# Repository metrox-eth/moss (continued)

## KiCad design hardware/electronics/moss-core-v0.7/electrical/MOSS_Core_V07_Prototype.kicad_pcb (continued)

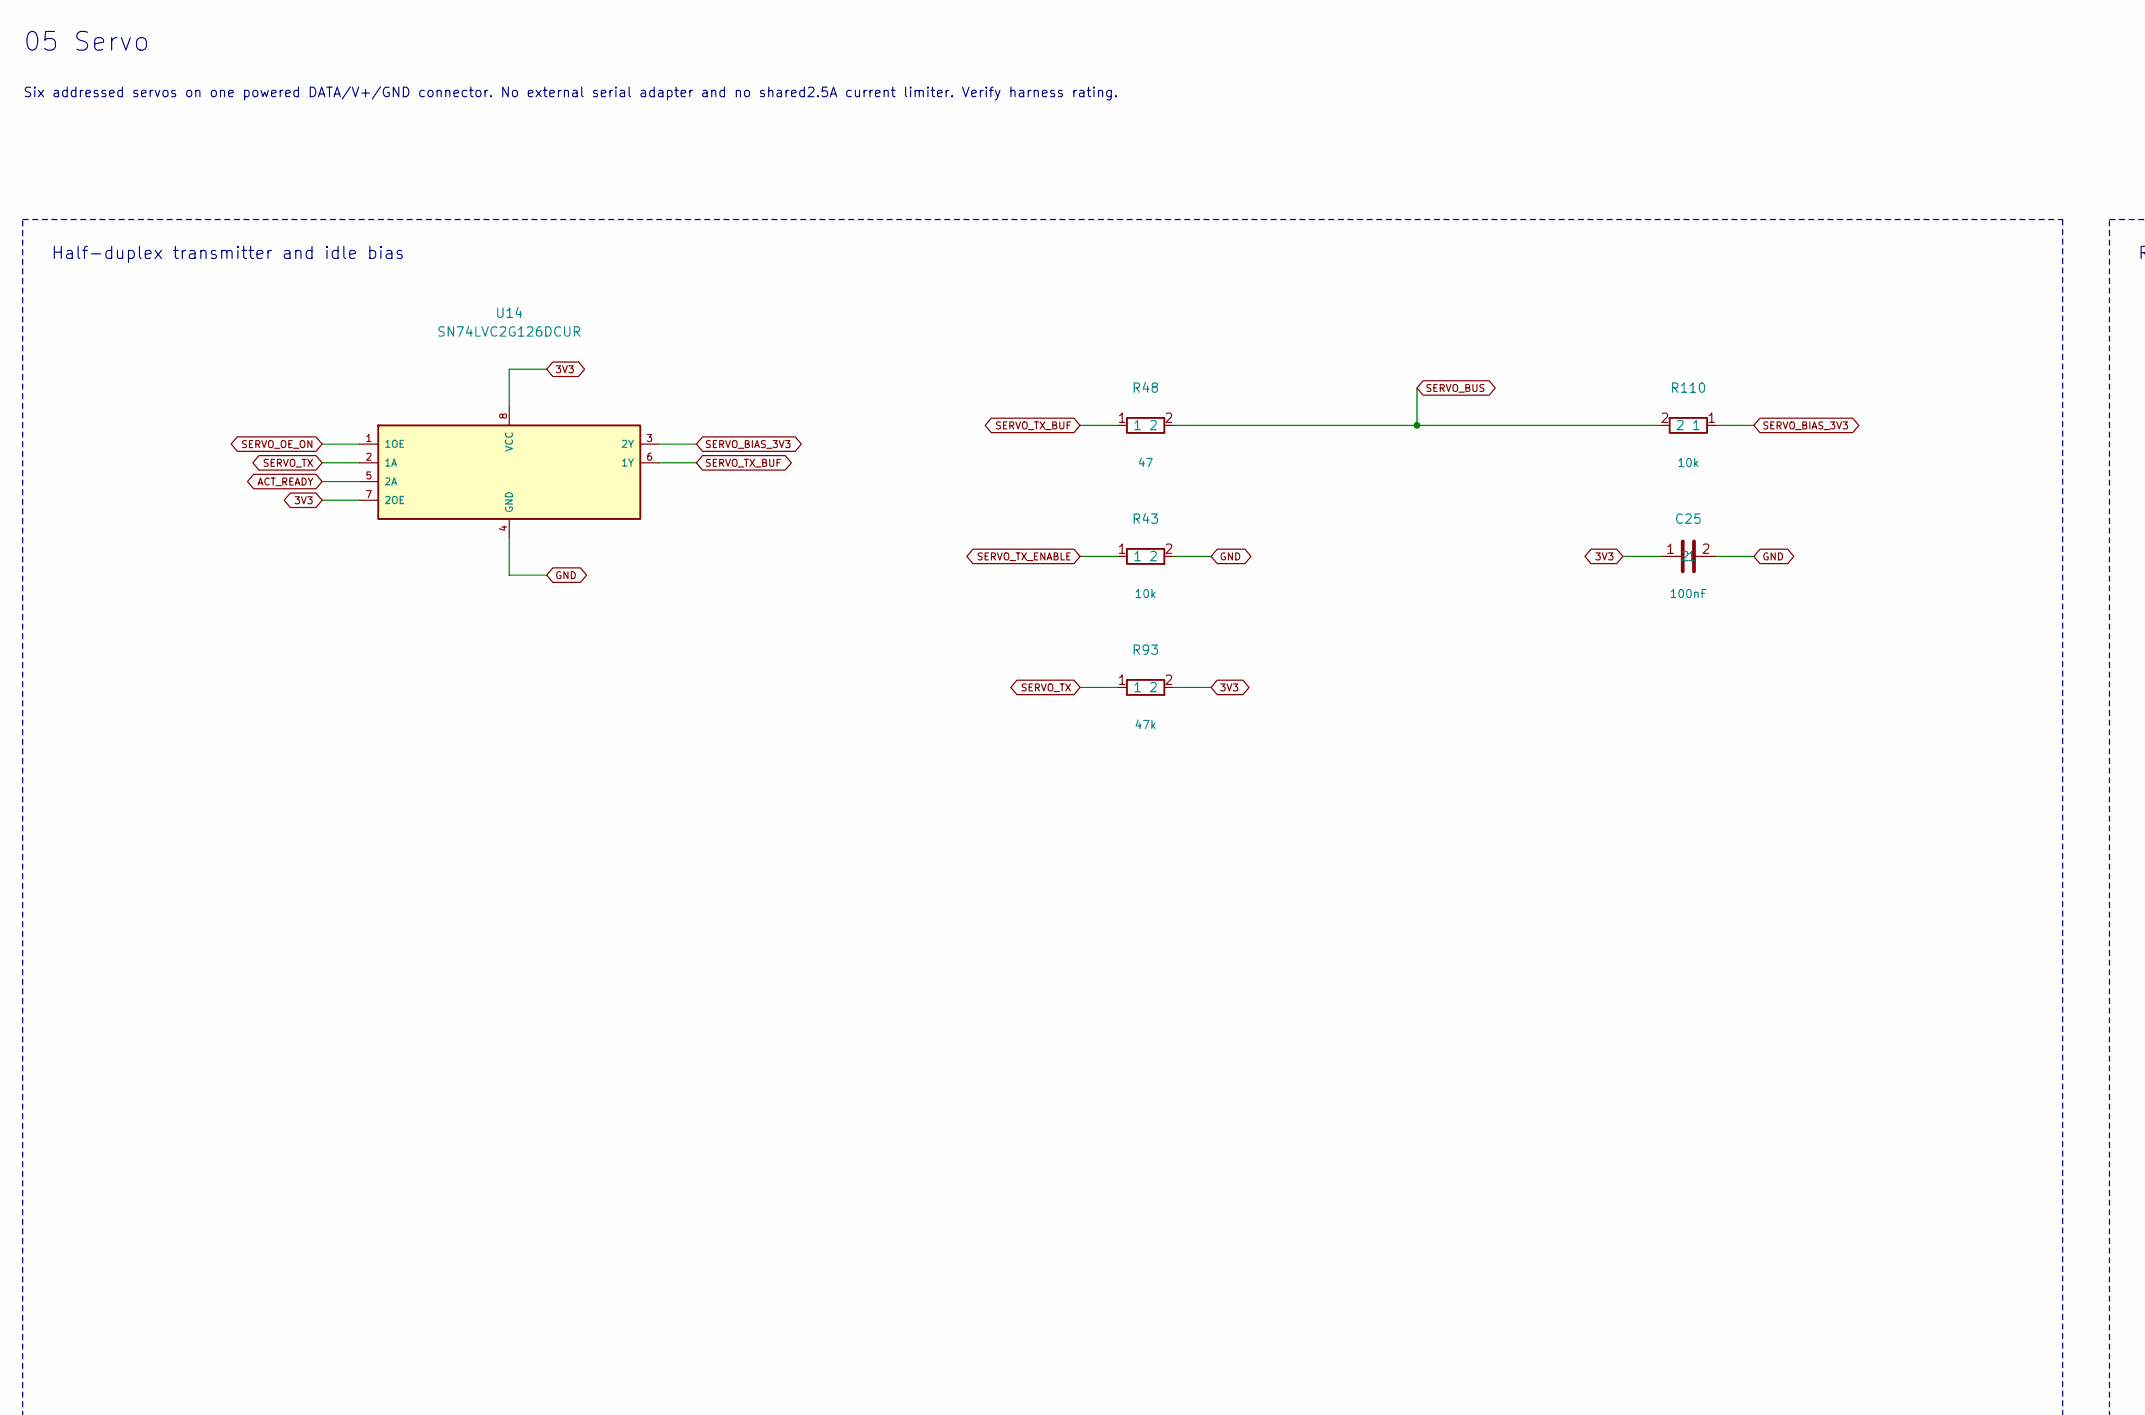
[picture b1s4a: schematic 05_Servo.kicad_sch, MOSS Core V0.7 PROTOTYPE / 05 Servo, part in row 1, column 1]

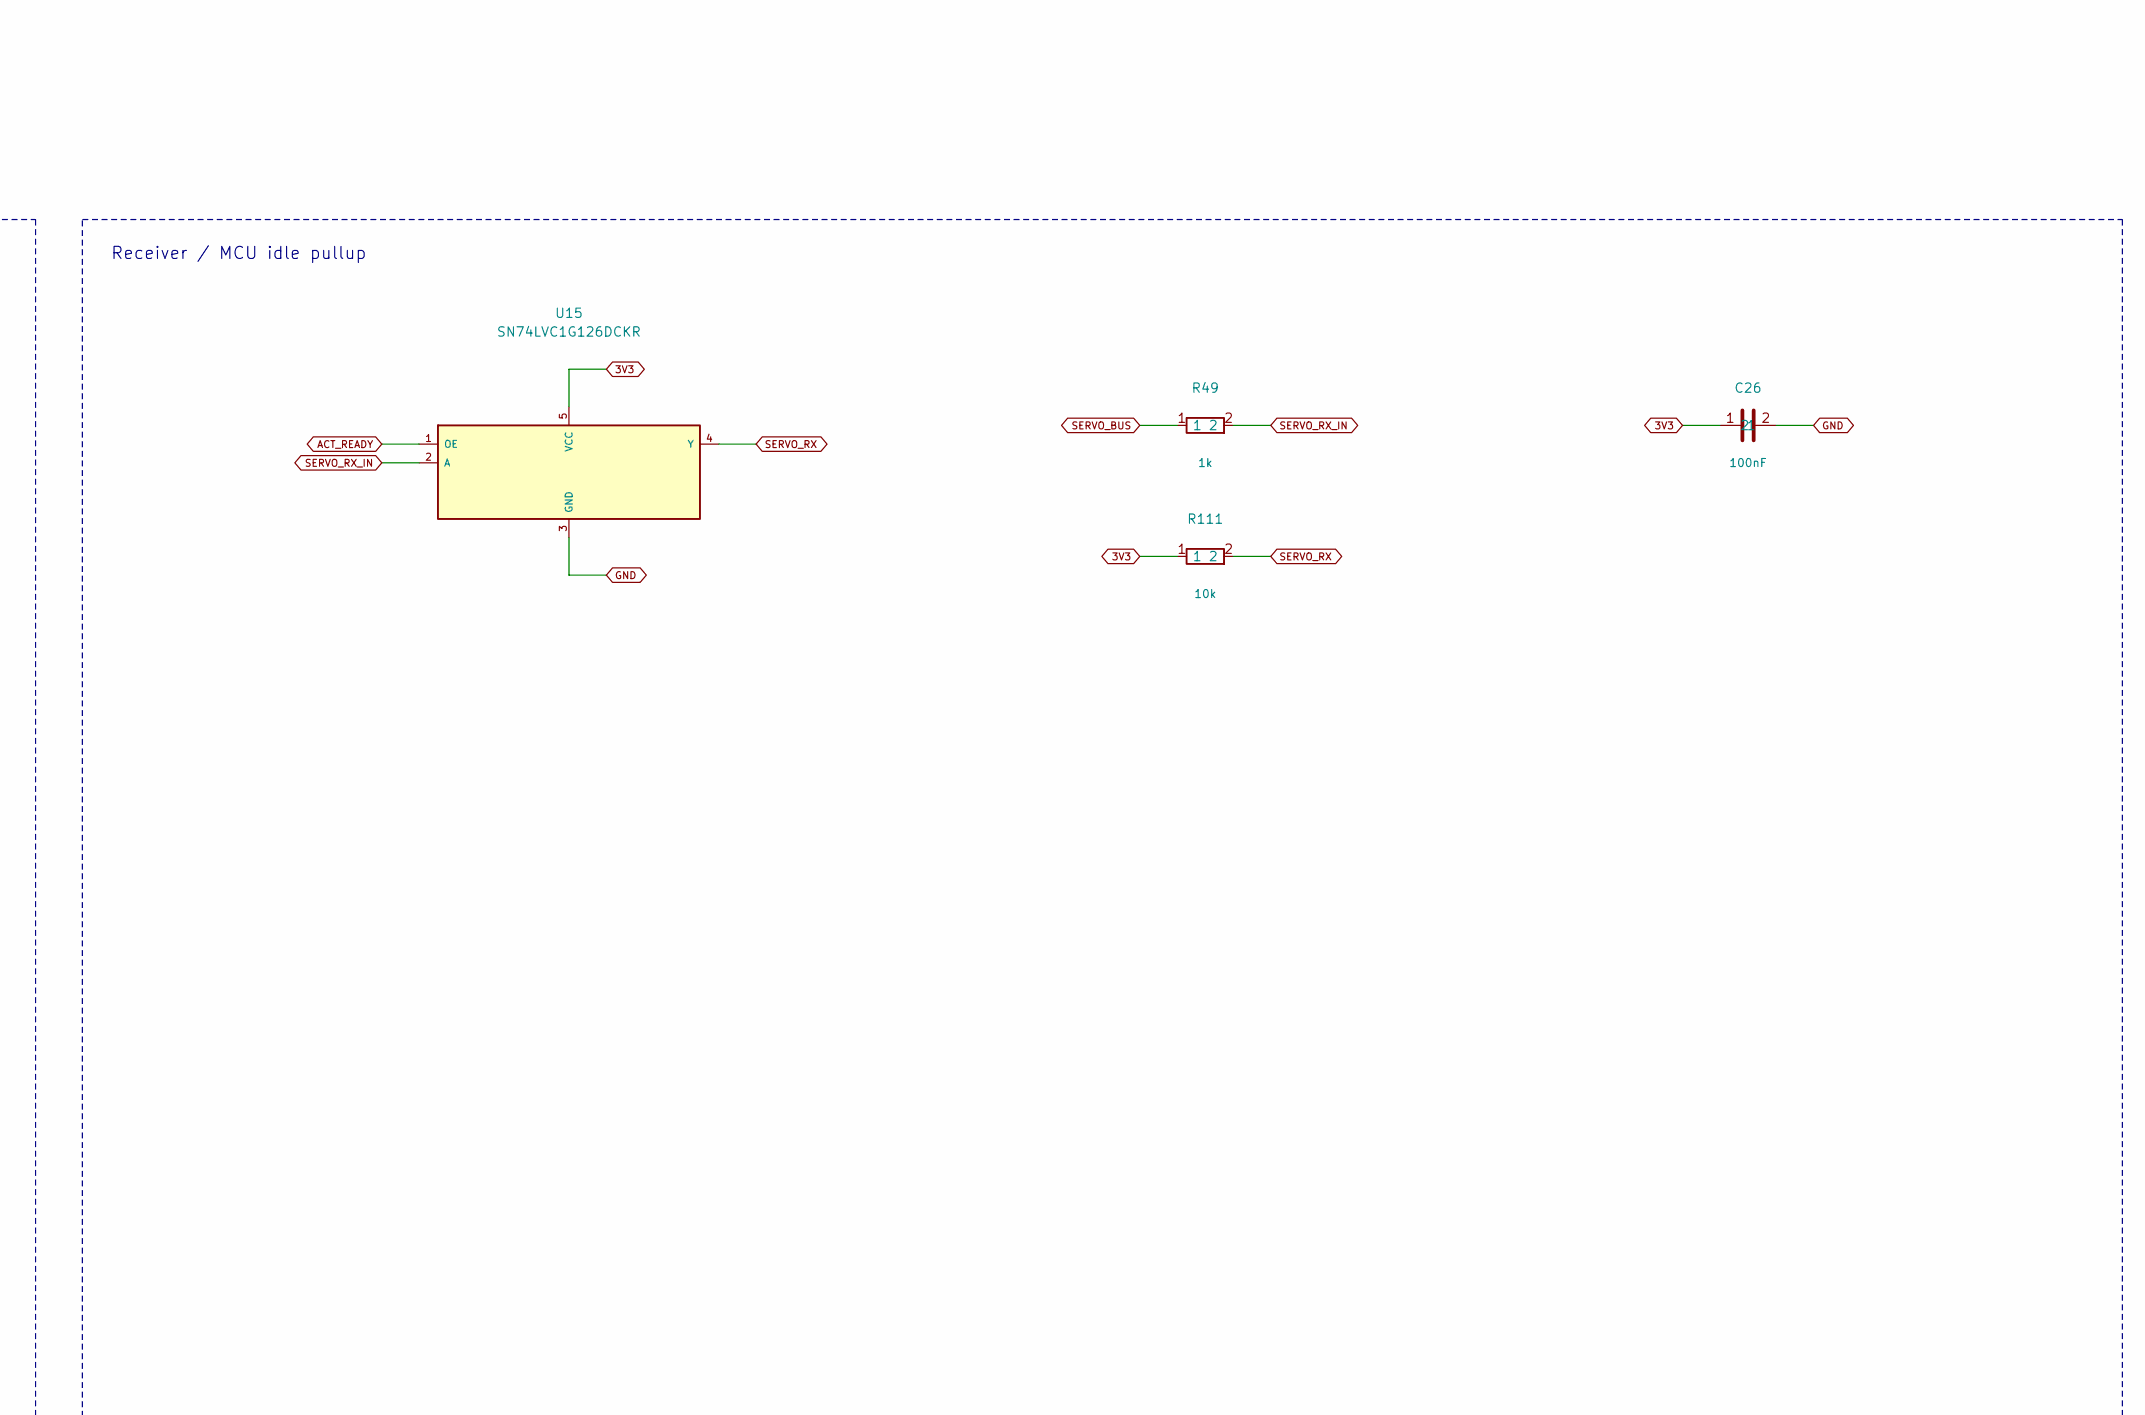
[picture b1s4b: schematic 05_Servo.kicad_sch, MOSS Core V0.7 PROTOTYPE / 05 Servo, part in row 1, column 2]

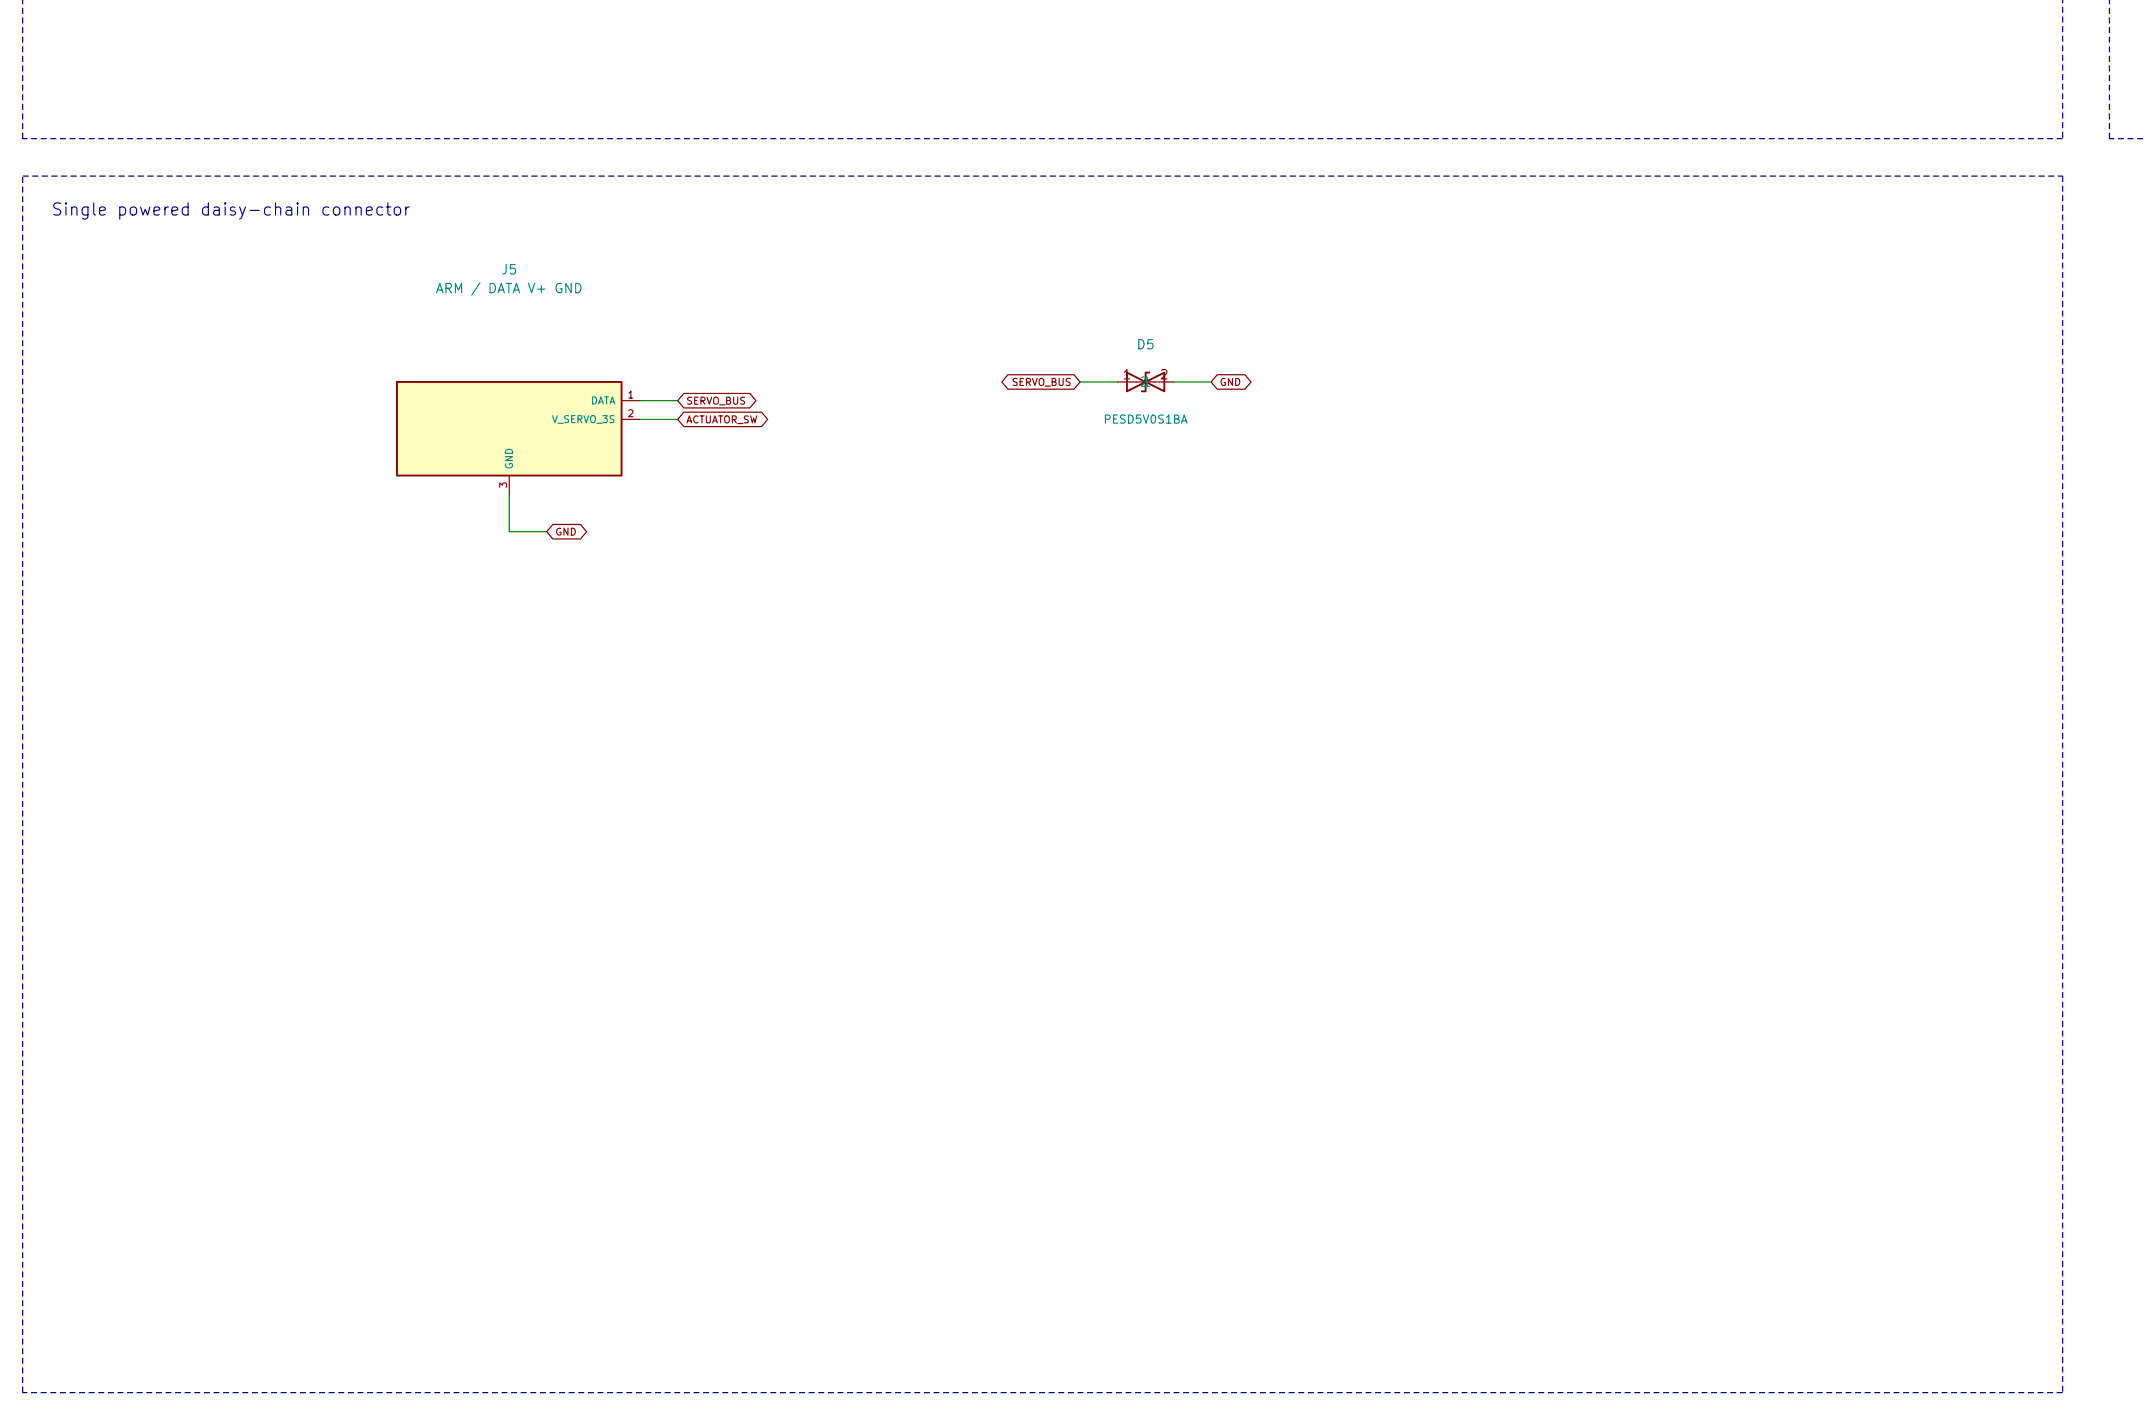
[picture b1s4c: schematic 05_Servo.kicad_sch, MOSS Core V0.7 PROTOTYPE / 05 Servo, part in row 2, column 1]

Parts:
C25, C26: 100nF; Capacitor_SMD_C_0603_1608Metric; MPN GRM188R71C104KA01D
D5: PESD5V0S1BA; Diode_SMD_D_SOD-323; MPN PESD5V0S1BA,115
J5: ARM / DATA V+ GND; Connector_Molex_Molex_SPOX_5267-03A_1x03_P2.50mm_Vertical; MPN 22-03-5035
R43, R110, R111: 10k; Resistor_SMD_R_0603_1608Metric; MPN RC0603FR-0710KL
R48: 47; Resistor_SMD_R_0603_1608Metric; MPN RC0603FR-0747RL
R49: 1k; Resistor_SMD_R_0603_1608Metric; MPN RC0603FR-071KL
R93: 47k; Resistor_SMD_R_0603_1608Metric; MPN RC0603FR-0747KL
U14: SN74LVC2G126DCUR; Package_SO_VSSOP-8_2.3x2mm_P0.5mm; MPN SN74LVC2G126DCUR
U15: SN74LVC1G126DCKR; Package_TO_SOT_SMD_SOT-353_SC-70-5; MPN SN74LVC1G126DCKR

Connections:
3V3: C25.1, C26.1, R93.2, R111.1, U14.7 (2OE), U14.8 (VCC), U15.5 (VCC); also elsewhere on the board
ACTUATOR_SW: J5.2 (V_SERVO_3S); also elsewhere on the board
GND: C25.2, C26.2, D5.2, J5.3 (GND), R43.2, U14.4 (GND), U15.3 (GND); also elsewhere on the board
SERVO_BIAS_3V3: R110.1, U14.3 (2Y)
SERVO_BUS: D5.1, J5.1 (DATA), R48.2, R49.1, R110.2
SERVO_OE_ON: U14.1 (1OE); also elsewhere on the board
SERVO_RX: R111.2, U15.4 (Y); also elsewhere on the board
SERVO_RX_IN: R49.2, U15.2 (A)
SERVO_TX: R93.1, U14.2 (1A); also elsewhere on the board
SERVO_TX_BUF: R48.1, U14.6 (1Y)
SERVO_TX_ENABLE: R43.1; also elsewhere on the board

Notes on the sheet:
05 Servo
Six addressed servos on one powered DATA/V+/GND connector. No external serial adapter and no shared2.5A current limiter. Verify harness rating.
Half-duplex transmitter and idle bias
Receiver / MCU idle pullup
Single powered daisy-chain connector

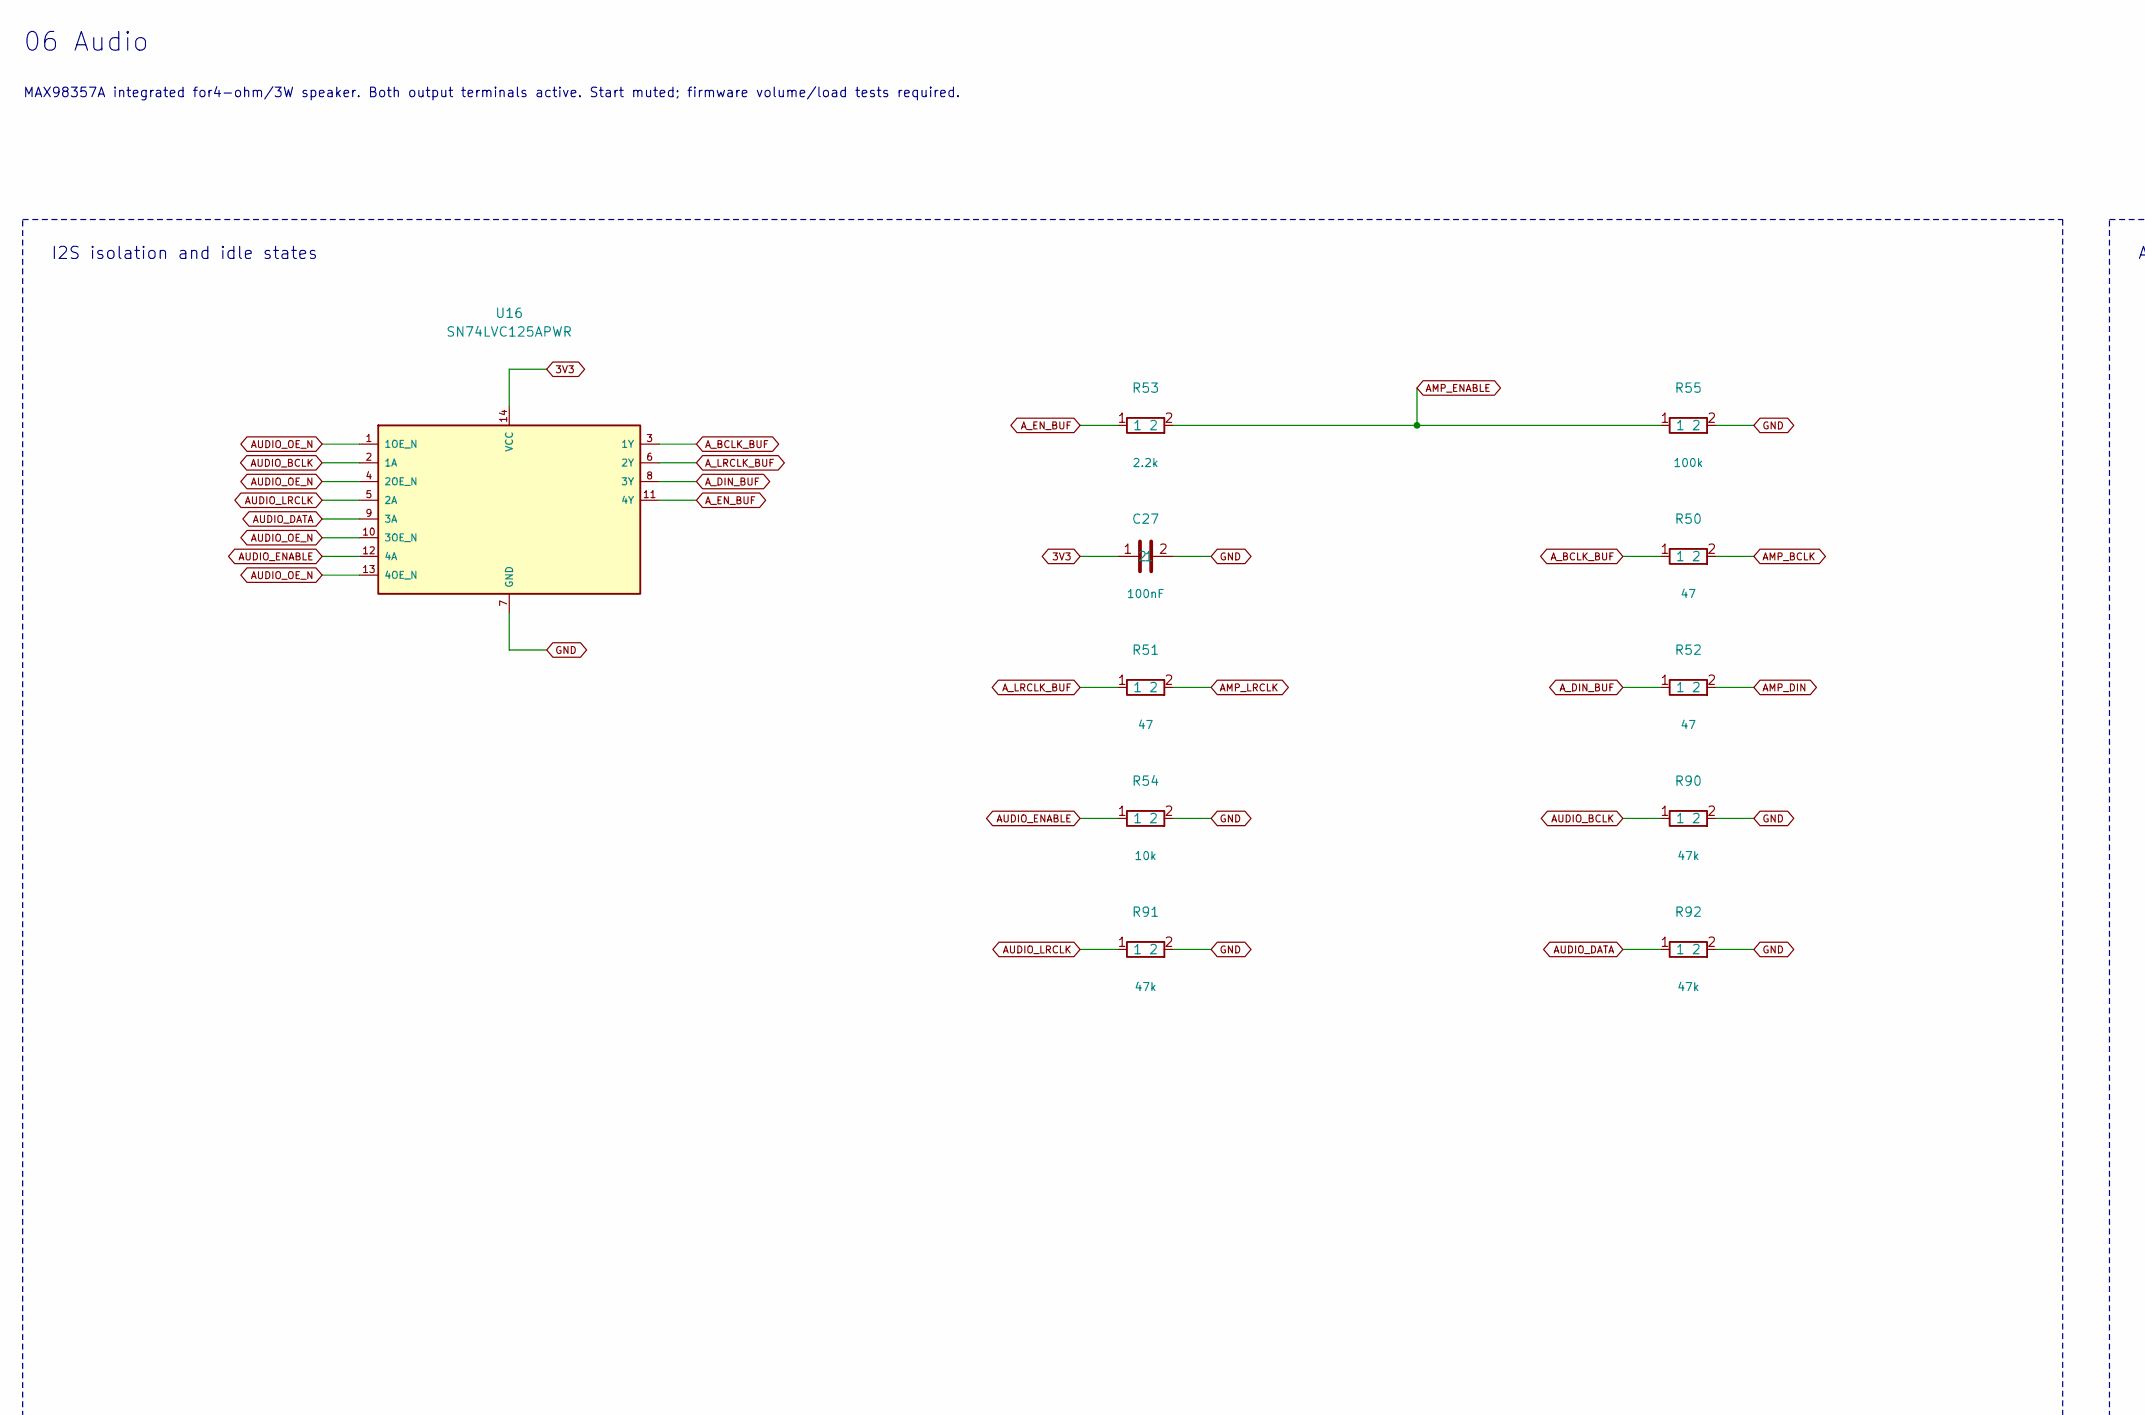
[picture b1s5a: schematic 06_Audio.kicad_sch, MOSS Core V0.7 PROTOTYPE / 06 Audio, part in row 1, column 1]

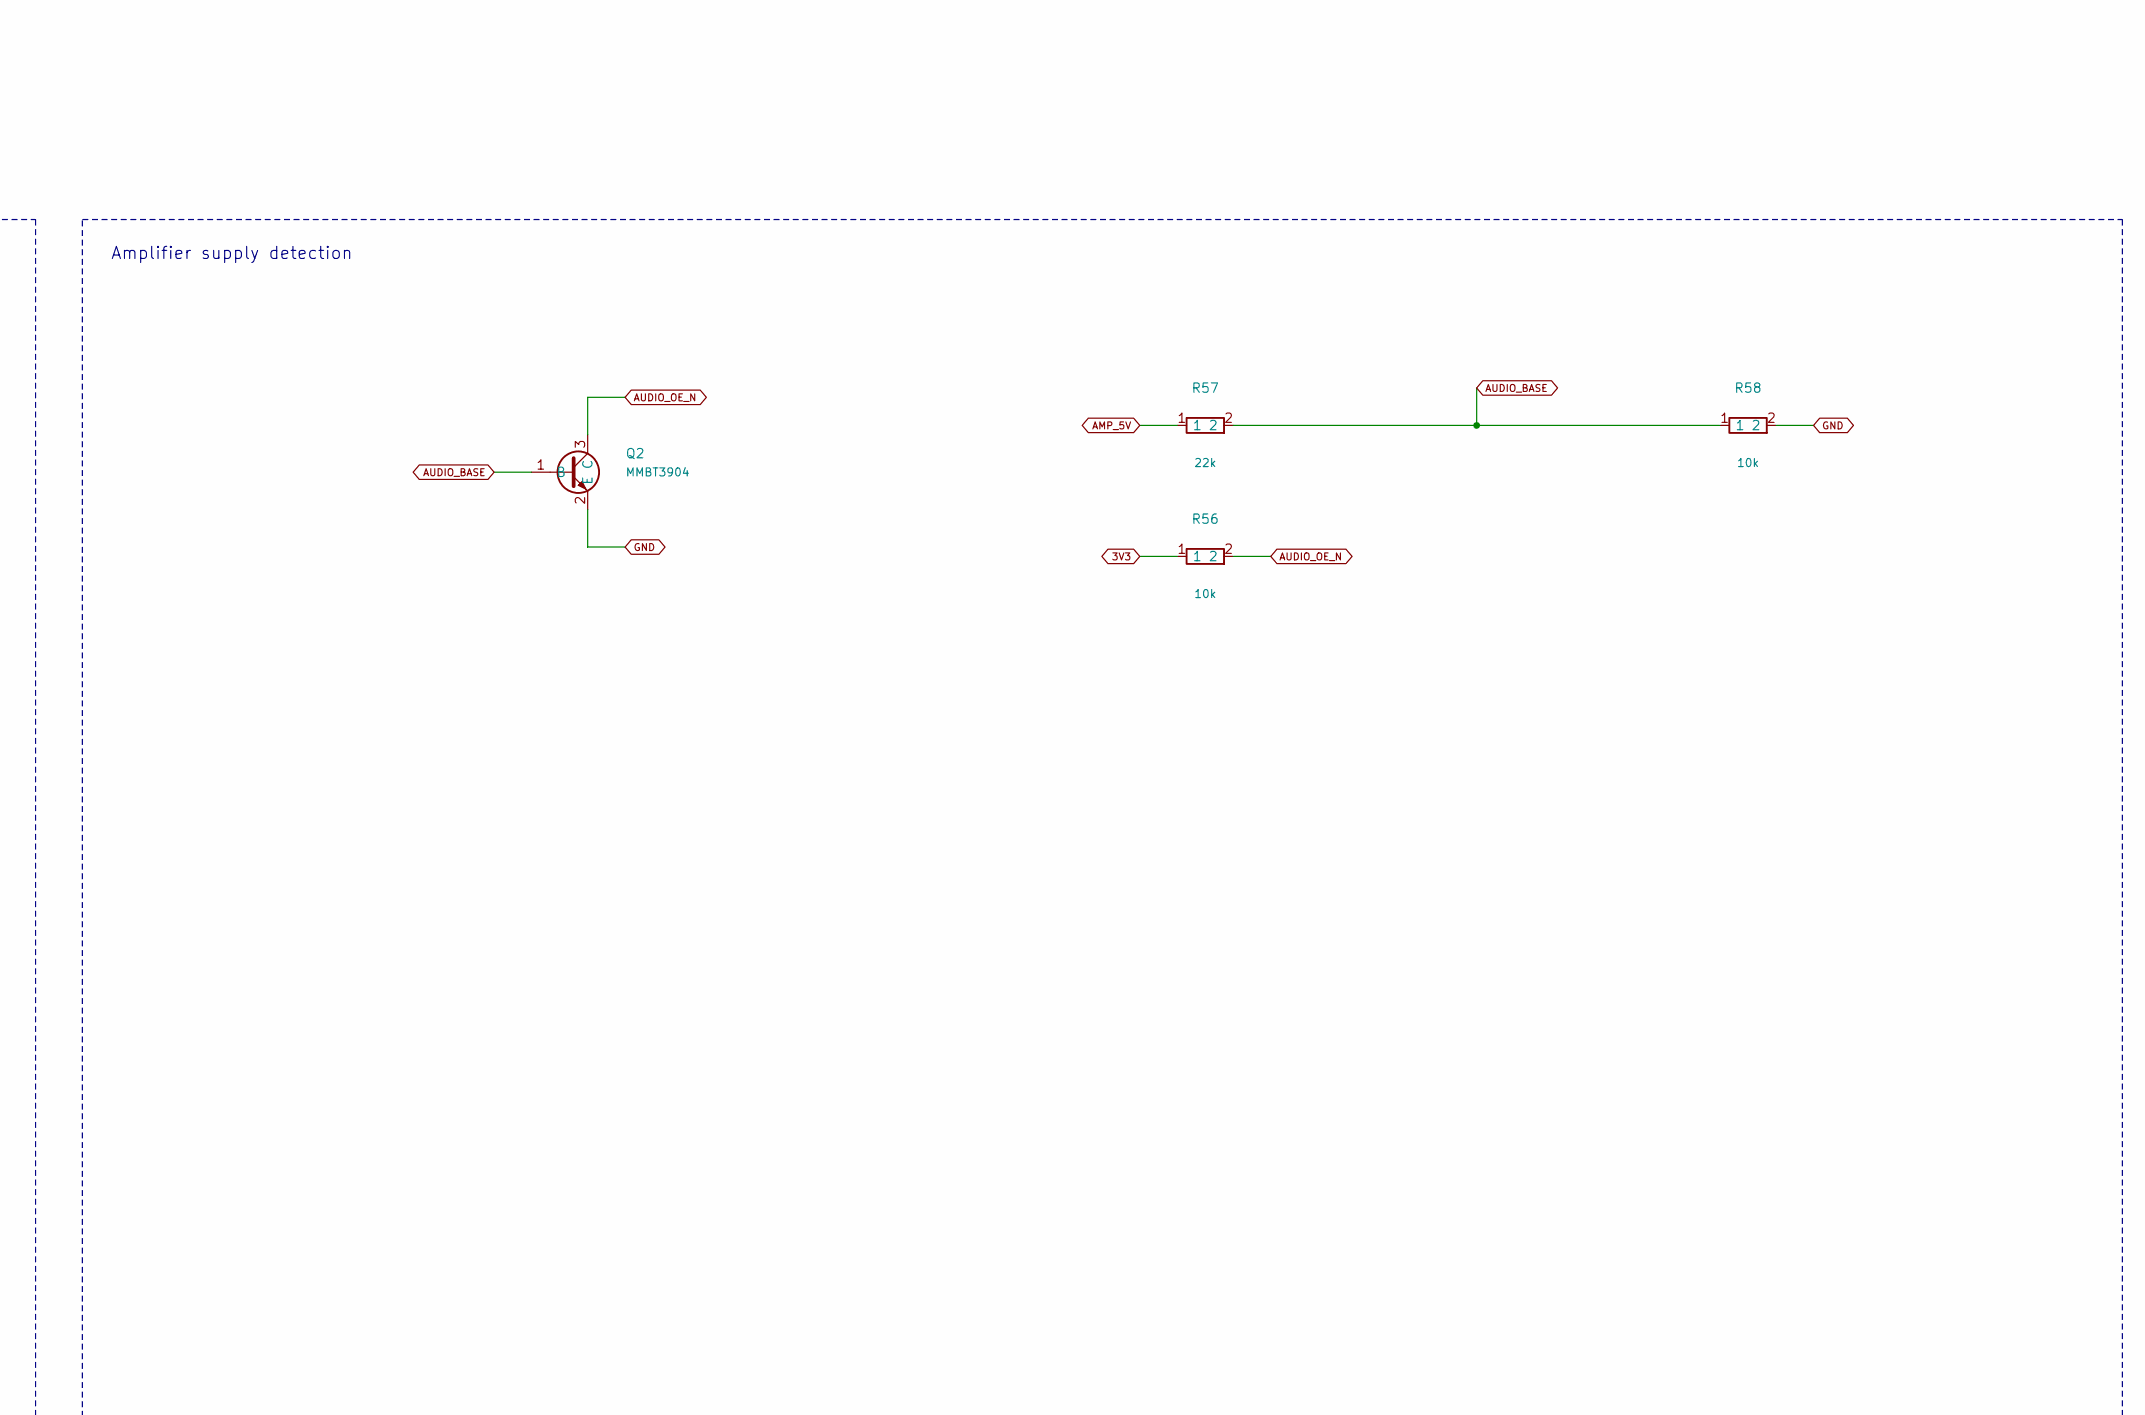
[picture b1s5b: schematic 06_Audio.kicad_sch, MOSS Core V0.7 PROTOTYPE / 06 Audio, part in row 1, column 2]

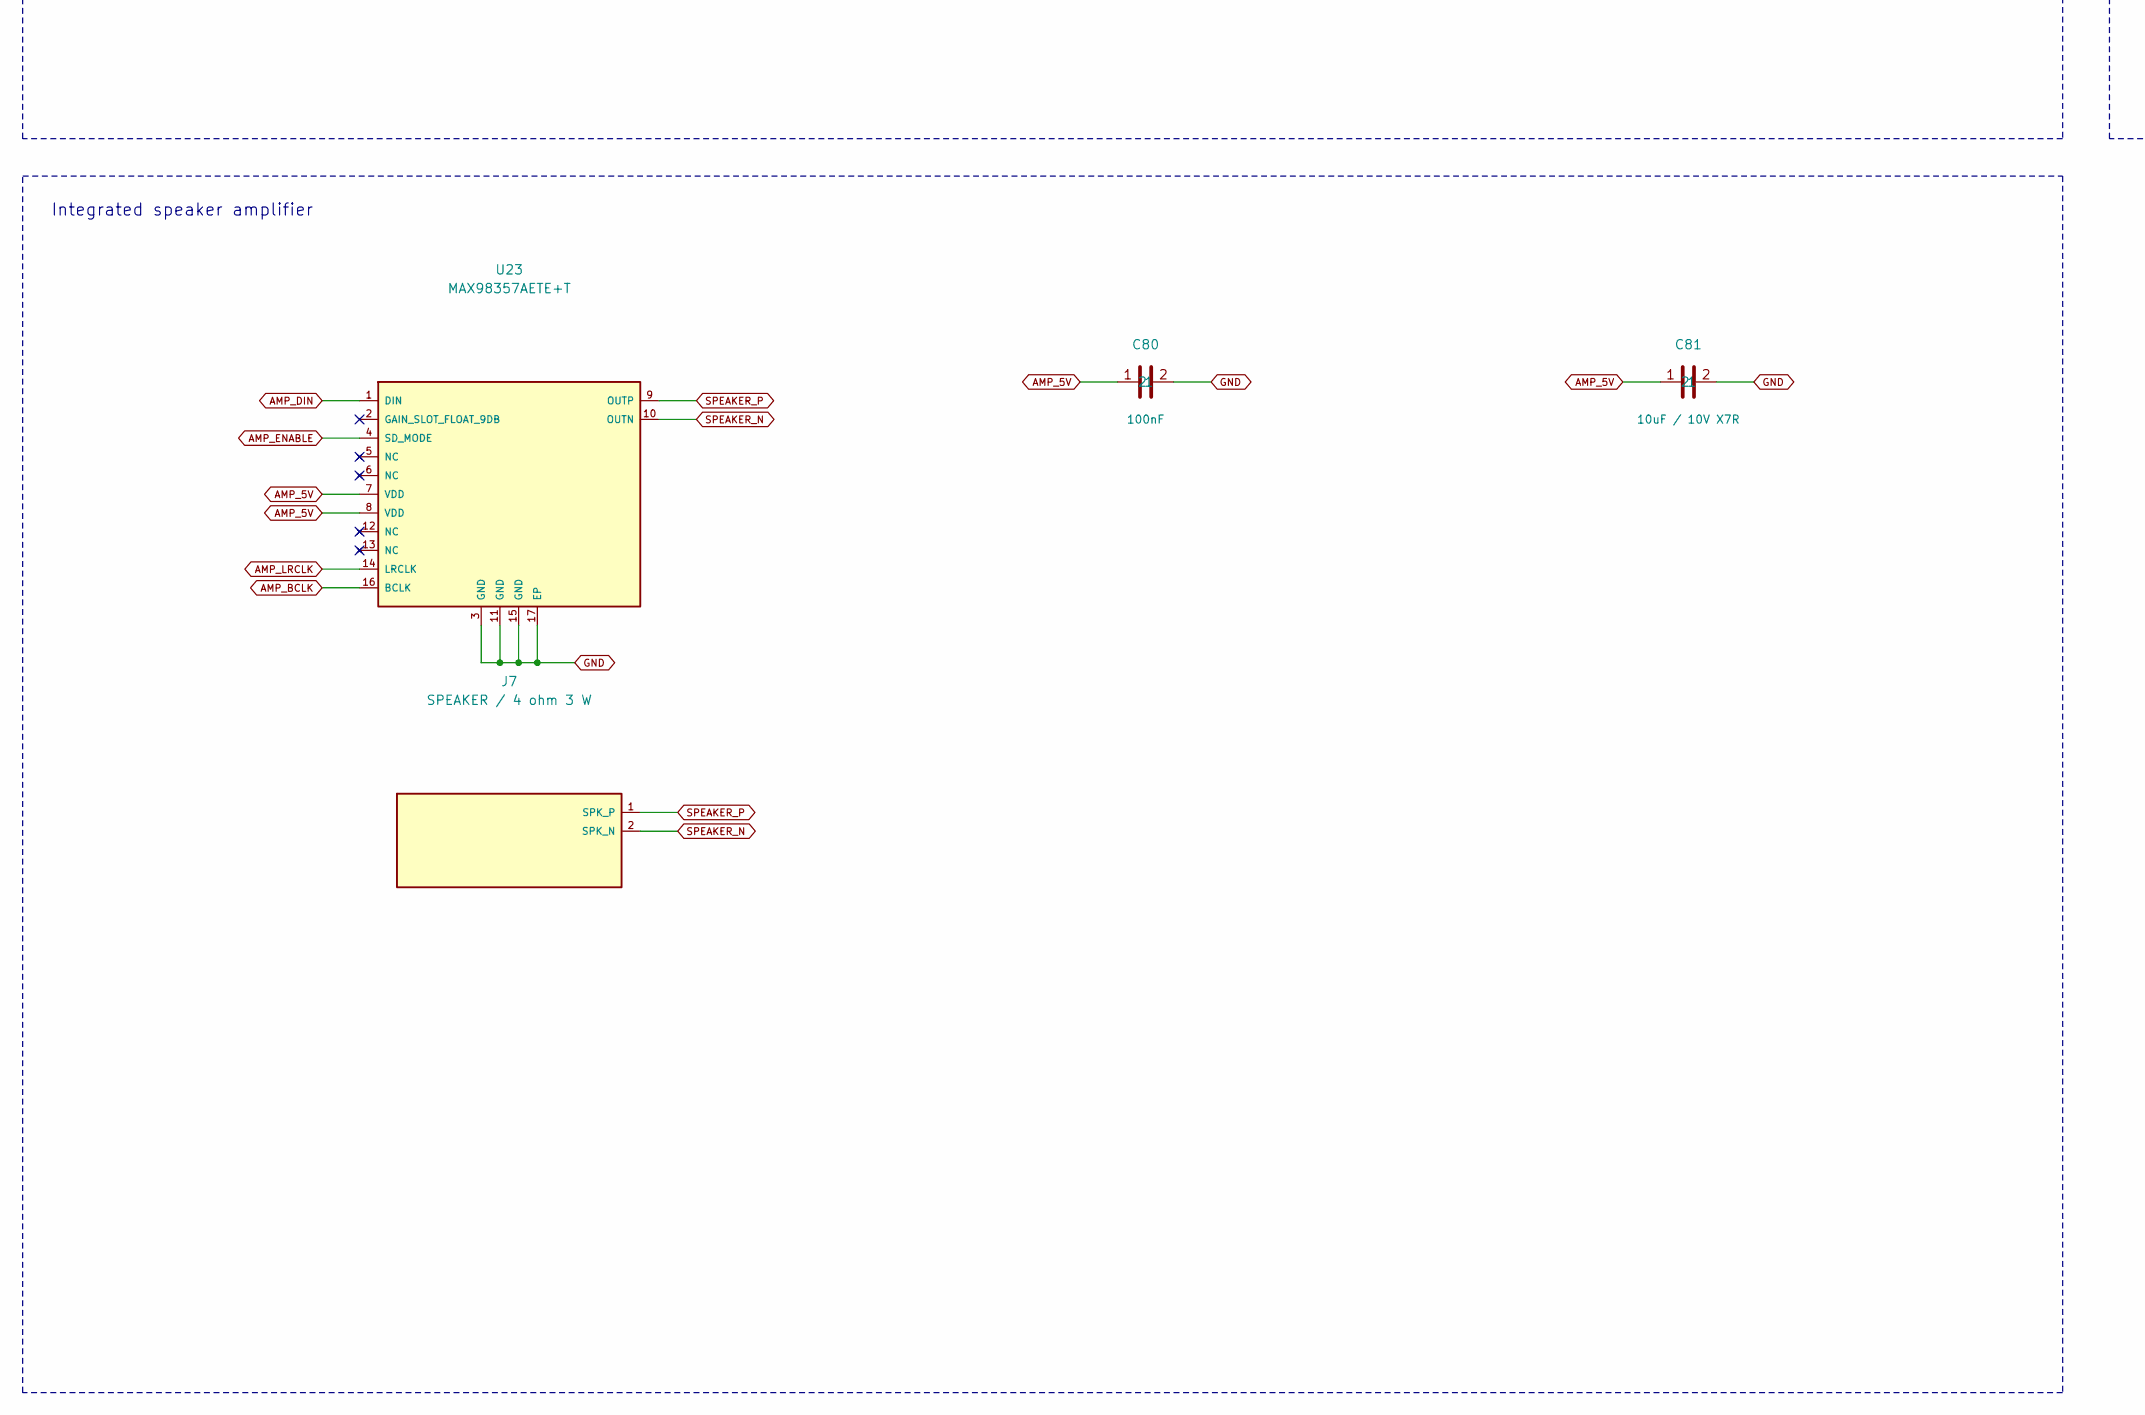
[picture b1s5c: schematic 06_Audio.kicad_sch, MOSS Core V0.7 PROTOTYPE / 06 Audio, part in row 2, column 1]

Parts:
C27, C80: 100nF; Capacitor_SMD_C_0603_1608Metric; MPN GRM188R71C104KA01D
C81: 10uF / 10V X7R; Capacitor_SMD_C_0805_2012Metric; MPN GRM21BR71A106KE51L
J7: SPEAKER / 4 ohm 3 W; Connector_JST_JST_PH_B2B-PH-K_1x02_P2.00mm_Vertical; MPN B2B-PH-K-S(LF)(SN)
Q2: MMBT3904; Package_TO_SOT_SMD_SOT-23; MPN MMBT3904,215
R50, R51, R52: 47; Resistor_SMD_R_0603_1608Metric; MPN RC0603FR-0747RL
R53: 2.2k; Resistor_SMD_R_0603_1608Metric; MPN RC0603FR-072K2L
R54, R56, R58: 10k; Resistor_SMD_R_0603_1608Metric; MPN RC0603FR-0710KL
R55: 100k; Resistor_SMD_R_0603_1608Metric; MPN RC0603FR-07100KL
R57: 22k; Resistor_SMD_R_0603_1608Metric; MPN RC0603FR-0722KL
R90, R91, R92: 47k; Resistor_SMD_R_0603_1608Metric; MPN RC0603FR-0747KL
U16: SN74LVC125APWR; Package_SO_TSSOP-14_4.4x5mm_P0.65mm; MPN SN74LVC125APWR
U23: MAX98357AETE+T; Package_DFN_QFN_MAX98357A_T1633_4_90_0031; MPN MAX98357AETE+T

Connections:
3V3: C27.1, R56.1, U16.14 (VCC); also elsewhere on the board
AMP_5V: C80.1, C81.1, R57.1, U23.7 (VDD), U23.8 (VDD); also elsewhere on the board
AMP_BCLK: R50.2, U23.16 (BCLK)
AMP_DIN: R52.2, U23.1 (DIN)
AMP_ENABLE: R53.2, R55.1, U23.4 (SD_MODE)
AMP_LRCLK: R51.2, U23.14 (LRCLK)
AUDIO_BASE: Q2.1 (B), R57.2, R58.1
AUDIO_BCLK: R90.1, U16.2 (1A); also elsewhere on the board
AUDIO_DATA: R92.1, U16.9 (3A); also elsewhere on the board
AUDIO_ENABLE: R54.1, U16.12 (4A); also elsewhere on the board
AUDIO_LRCLK: R91.1, U16.5 (2A); also elsewhere on the board
AUDIO_OE_N: Q2.3 (C), R56.2, U16.1 (1OE_N), U16.4 (2OE_N), U16.10 (3OE_N), U16.13 (4OE_N)
A_BCLK_BUF: R50.1, U16.3 (1Y)
A_DIN_BUF: R52.1, U16.8 (3Y)
A_EN_BUF: R53.1, U16.11 (4Y)
A_LRCLK_BUF: R51.1, U16.6 (2Y)
GND: C27.2, C80.2, C81.2, Q2.2 (E), R54.2, R55.2, R58.2, R90.2, R91.2, R92.2, U16.7 (GND), U23.3 (GND), U23.11 (GND), U23.15 (GND), U23.17 (EP); also elsewhere on the board
SPEAKER_N: J7.2 (SPK_N), U23.10 (OUTN)
SPEAKER_P: J7.1 (SPK_P), U23.9 (OUTP)

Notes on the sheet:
06 Audio
MAX98357A integrated for4-ohm/3W speaker. Both output terminals active. Start muted; firmware volume/load tests required.
I2S isolation and idle states
Amplifier supply detection
Integrated speaker amplifier
